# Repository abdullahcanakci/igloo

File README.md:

I have one of those led strips which controlled with a colorful remote and shows you the rainbow. I like them, setting the mood up so I can spend time on dark themed environments, or not having to get up after I'm done for the night and want some sleep.
But I think they lack some of those IOT and modern electronics magic we get used to. I only have cheap ones, not those philips hue or some other brand. 
The ones I have, has 20 preconfigured color and 4 different seizure inducing modes, can alter brightness. Everthing is fine and dandy. But if you want to have another color, too bad. Want to turn your home something other than a disco, no mode for that.

In my mind perfect control device should have:
1. Can alter colors without any limit.
2. Can alter modes without any limit.
3. Set auto on-off setting.
4. Can controlled from old school remotes.
5. Integration.

## 1 - Coloring

It just PWM how hard can it be. 

Right now I'm leaning into 3 color channels + 1 common channel. From my market search most of these strips are common VCC and RGB, there are some RGBW but not really widespread, at least in my country.

## 2 - Modes

The ones I have seen have

- Strobe
- Fade
- Ones above but with different colors.

I think these are not really nice modes, fade is somewhat bearable. Having ability to change fade colors, times and looping would be great, one can achieve so much with mere settings. 

## 3 - Auto

Automatic off would be nice set a timeout and let it fade out, or set a timer and wake up to fake sunset in the middle of winter.

## 4 - Remote

Although having a network connection is great we can't be certain a networked device would be avaible for, this reason there should be sane defaults, and ability to set any random IR remote as remote would be great. 

## 5 - Integration

I though about a bit about how can I implement multi device, controller etc in a system only composed of ESP12. It is not actually hard, but I didn't like the complexity of doing it all in C++, with some half-baked http library.

Thinking about Raspberry Pi Mini, an idea occurred, lets make a rPi a host, that applicable devices can connect, this way, I only need to create a web server to handle "User Interaction" on rPi, and it will pass down relevant data to controllers. This way I don't have to implement so much in ESP12's constraints. This has significant positives:

- Only need to create one web app to handle multi devices.
- Ease of adding and removing devices to system
  - Old way, I have to add a device to a network and set it up, and use it alone. This way, a newly added device can search the network for a compliant device and set up a connection and set the device up. After we can manage the controller device with the unified webapp.
- Ease of extensibility. 
  - Host system can be updated to handle more types of devices.
  - Host can be changed with a compliant system.
  - Host can implement third party home automation systems.
- Can update controller systems through air? Should be possible, have seen it, need to check how to implement it.

## Hardware

I have a look at some devices to use

- Raspberry Pi mini as host device. May create a hat for it to act as also, but not really sure about it.

- ESP12, is a good choice for sole pwm controlling job. It can do 200Hz refresh rate with 5ms downtime with software pwm. For hardware pwm, it has limited(2?) channels and not enough PWM counters to handle 3 different pwm channels.
- IRLML0030TRBF (TR Tape reel, BF ?), is a great little mosfet.
  - SOT23, so small
  - V_gth = 2.9V, which is great for most microcontrollers
  - Rds_on = 40mΩ @ 4.5V up to 4.2 amp continuos current. Which is plenty. Will mean ~50W @ 12V per channel. Prolly should limit it about 30W for 10 meter of 3W/m strip per channel.
  - PD of 0.65W @3.3V gate voltage 4 amp current, which will create a junction temperature of 65°C over ambient.
  - Not expensive @ 0.42$ per piece.
- Board will be 2 layers, preferably smaller than 40x60mm.

### Hardware Design

---

I have finally finished the hardware for led controller. It took some time, but I'm happy with the final product. While I was on the drawing board, I considered driving mosfets with pins from ESP12, which would work fine. But the specifications of the mosfet only provides values down to 4.5V which is 33mΩ. At 3.3V I was not in a safe spot to use the mosfet to it's limits. So I constructed a front end for every channel which consists of 1 PNP and 1 NPN transistor and few resistors. This enabled me to raise gate voltage of the mosfet to ~10.8V which Rds<sub>on</sub> = 22mΩ. Reduces resistance will achieve better thermals duty cycle is close to %100. Also by using transistors, mosfet gate charge time will be shorter which means mosfet will spend less time on the high resistance zones which also will help me to achieve better thermals. Cost for the extra transistors is negligible. They cost about 0.10$ to 0.15$ per 20 to 25 piece.

Final board size ended up at 50mm by 55mm which is great. While designing the board 40x60 was a bit optimistic but in the end it is only off by %15.

Power dissipation is fine at 10.8V gate voltage, 5.2A current. Resistive losses are @ 0.89W which will raise temperature to 90°C over ambient. Switching losses should be fine. By using transistors I reduced time to charge the gate capacitor. Also ESP12 will most likely run the PWM @ 1KHz which is pretty low, in this situation resistive losses will be the driving force. 

I used [this](https://www.electronicdesign.com/boards/calculate-dissipation-mosfets-high-power-supplies) website to help me with power dissipation.

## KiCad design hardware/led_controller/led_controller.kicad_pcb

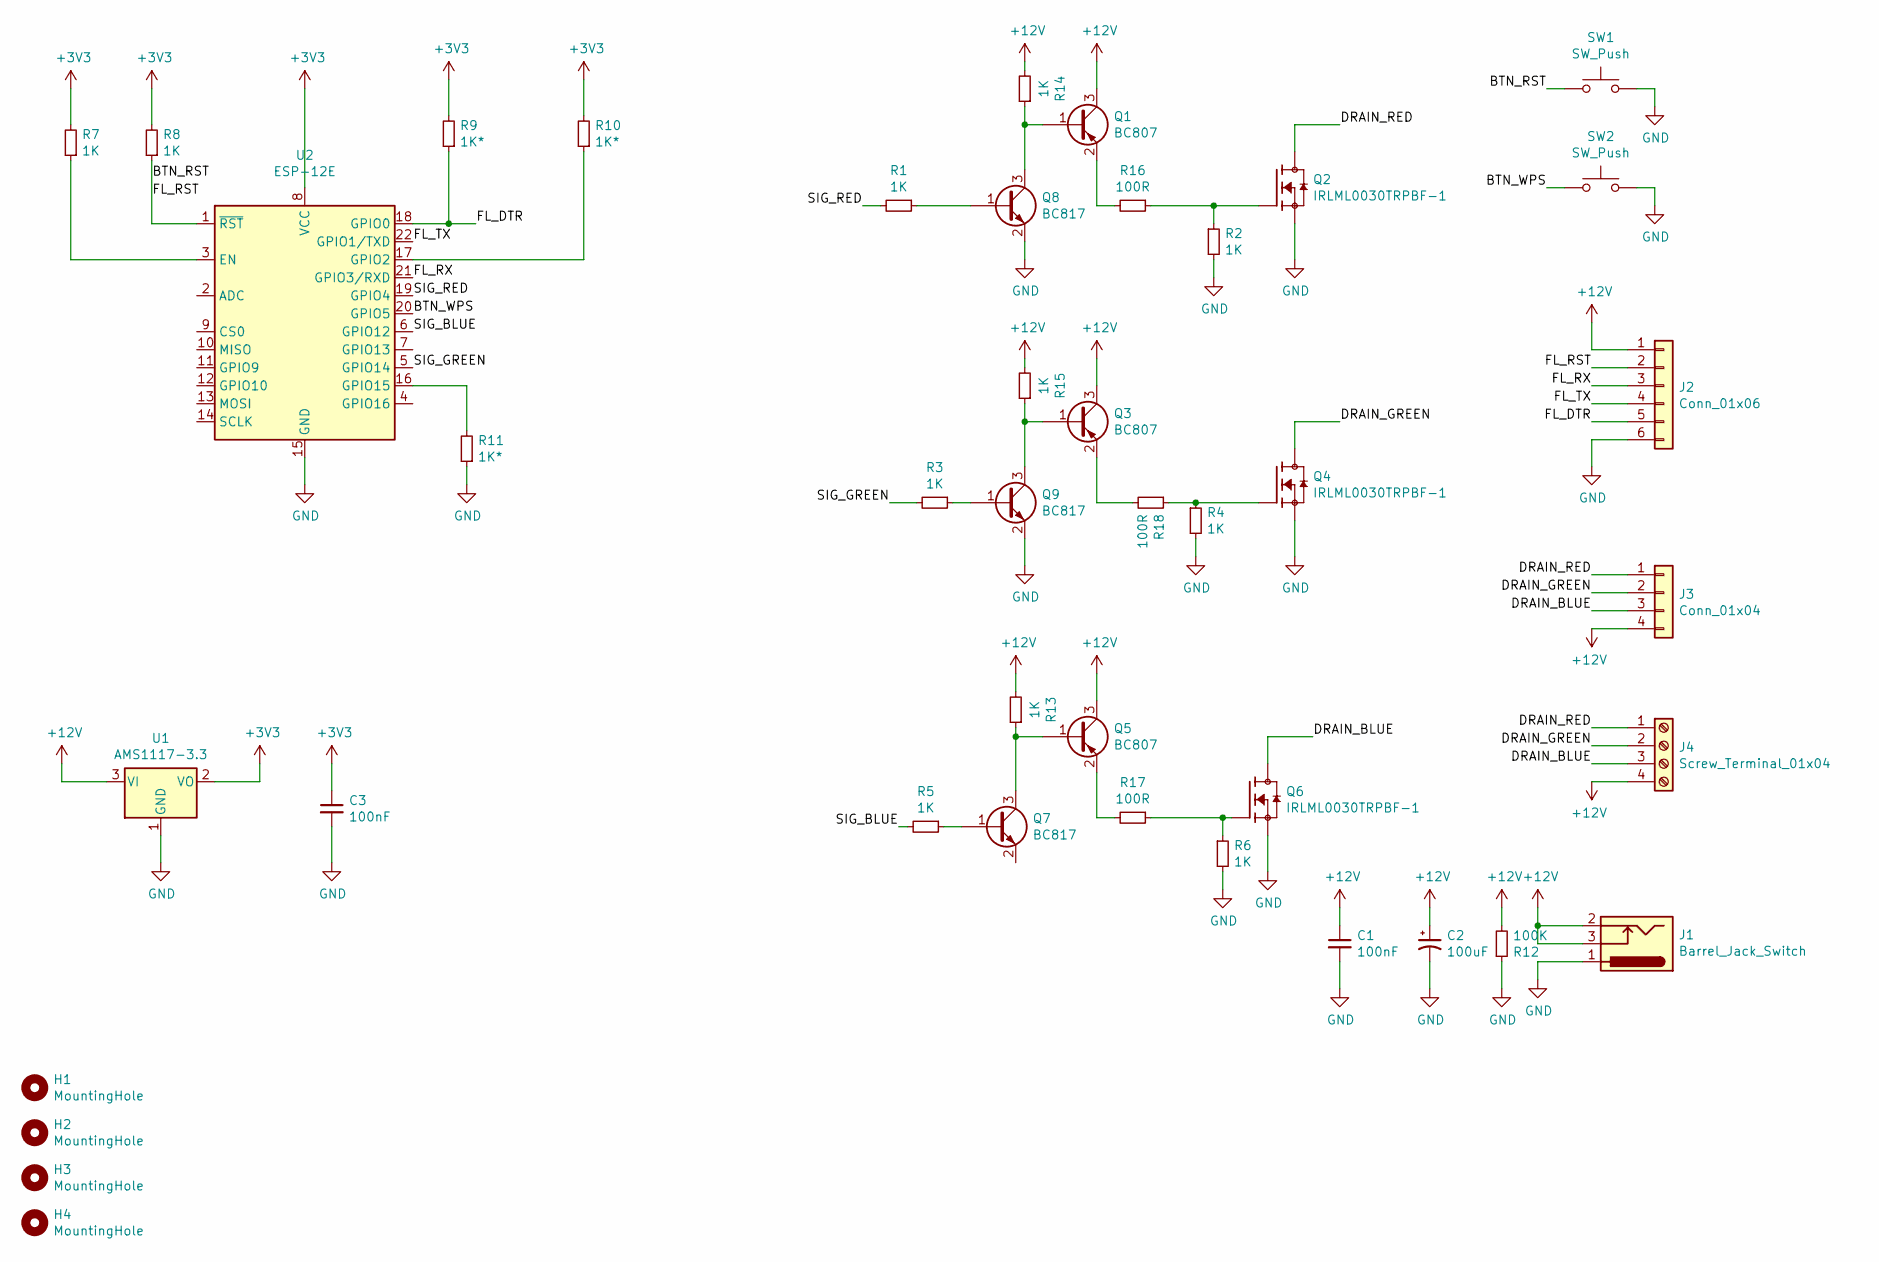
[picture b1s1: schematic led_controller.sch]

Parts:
C1, C3: 100nF; C_0805_2012Metric_Pad1.15x1.40mm_HandSolder
C2: 100uF; CP_Radial_D10.0mm_P2.50mm_P5.00mm
H1, H2, H3, H4: MountingHole; MountingHole_3.2mm_M3
J1: Barrel_Jack_Switch; BarrelJack_Horizontal
J2: Conn_01x06; PinHeader_1x06_P2.54mm_Vertical
J3: Conn_01x04; PinHeader_1x04_P2.54mm_Vertical
J4: Screw_Terminal_01x04; TerminalBlock_RND_205-00047_1x04_P5.00mm_Horizontal
Q1, Q3, Q5: BC807; SOT-23
Q2, Q4, Q6: IRLML0030TRPBF-1; SOT95P237X112-3N
Q7, Q8, Q9: BC817; SOT-23
R1, R2, R3, R4, R5, R6, R7, R8, R13, R14, R15: 1K; R_0805_2012Metric_Pad1.15x1.40mm_HandSolder
R9, R10, R11: 1K*; R_0805_2012Metric_Pad1.15x1.40mm_HandSolder
R12: 100K; R_0805_2012Metric_Pad1.15x1.40mm_HandSolder
R16, R17, R18: 100R; R_0805_2012Metric_Pad1.15x1.40mm_HandSolder
SW1, SW2: SW_Push; SW_Push_1P1T_NO_6x6mm_H9.5mm
U1: AMS1117-3.3; SOT-223-3_TabPin2
U2: ESP-12E

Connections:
+3V3: C3.1, R7.2, R8.2, R9.2, R10.2, U1.2 (VO), U2.8 (VCC)
+12V: C1.1, C2.1, J1.2, J1.3, J2.1, J3.4, J4.4, Q1.3 (C), Q3.3 (C), Q5.3 (C), R12.2, R13.2, R14.2, R15.2, U1.3 (VI)
/BTN_RST: J2.2, R8.1, SW1.1, U2.1 (~RST)
/BTN_WPS: SW2.1, U2.20 (GPIO5)
/DRAIN_BLUE: J3.3, J4.3, Q6.3 (D)
/DRAIN_GREEN: J3.2, J4.2, Q4.3 (D)
/DRAIN_RED: J3.1, J4.1, Q2.3 (D)
/FL_DTR: J2.5, R9.1, U2.18 (GPIO0)
/FL_RX: J2.3, U2.21 (GPIO3/RXD)
/FL_TX: J2.4, U2.22 (GPIO1/TXD)
/SIG_BLUE: R5.2, U2.6 (GPIO12)
/SIG_GREEN: R3.2, U2.5 (GPIO14)
/SIG_RED: R1.2, U2.19 (GPIO4)
GND: C1.2, C2.2, C3.2, J1.1, J2.6, Q2.2 (S), Q4.2 (S), Q6.2 (S), Q8.2 (E), Q9.2 (E), R2.2, R4.2, R6.2, R11.1, R12.1, SW1.2, SW2.2, U1.1 (GND), U2.15 (GND)
unnamed: Q1.1 (B), Q8.3 (C), R14.1
unnamed: Q1.2 (E), R16.2
unnamed: Q2.1 (G), R2.1, R16.1
unnamed: Q3.1 (B), Q9.3 (C), R15.1
unnamed: Q3.2 (E), R18.2
unnamed: Q4.1 (G), R4.1, R18.1
unnamed: Q5.1 (B), Q7.3 (C), R13.1
unnamed: Q5.2 (E), R17.2
unnamed: Q6.1 (G), R6.1, R17.1
unnamed: Q7.1 (B), R5.1
unnamed: Q8.1 (B), R1.1
unnamed: Q9.1 (B), R3.1
unnamed: R7.1, U2.3 (EN)
unnamed: R10.1, U2.17 (GPIO2)
unnamed: R11.2, U2.16 (GPIO15)

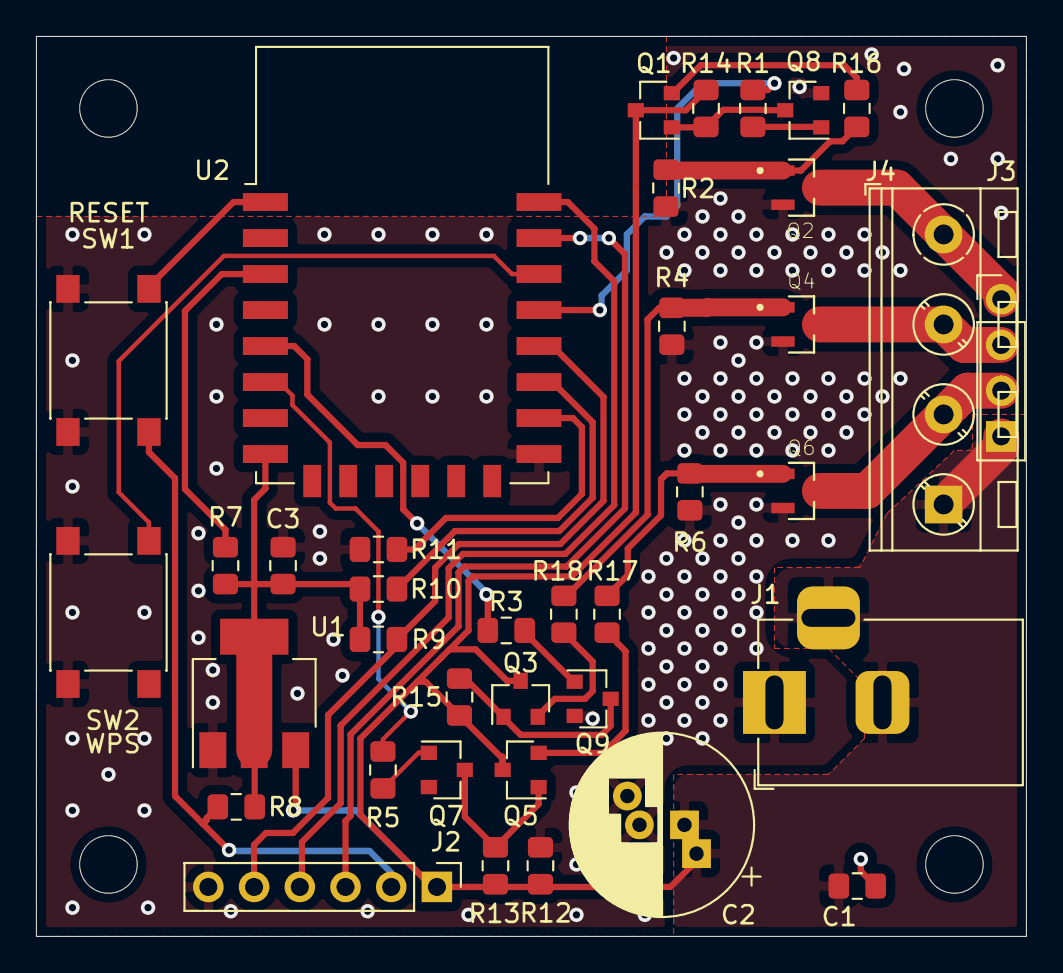
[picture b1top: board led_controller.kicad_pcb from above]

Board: 2 copper layers, 55.0 x 50.0 mm, 42 parts (0 on the bottom side), 29 nets.

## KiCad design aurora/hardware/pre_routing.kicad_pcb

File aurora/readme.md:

# Preface

I have one of those led strips with a colorful remote to control it. Most people have them, they are cheap, they are easy to install and most important of all abundant.

If I have to find a problem with them, it would be their horrendous controls. They have all the colors needed for full spectrum color creation, but their control circuitry only allows about 20 colors and 10 brightness settings.

I would like to have a controller with precise color control,  multiple modes to use and somewhat smart so it can act on predefined triggers.

Aim of the Aurora project is to create a led strip controller.

[Workspace Set-up](workspace.md)

## Requirements

1. High color range.
2. Multiple modes to use.
3. Actions by predefined triggers.
4. Integrated or solo use.
5. Preferably remote controlled.

### Led Control

Most of the generic led strips I have found contains RGB sink channels and 1 common VCC one. These are generally powered by 12V dedicated power supplies. There are some 4 color strips which includes white but they are not really common.

Each color channel will be controlled by a dedicated mosfet circuitry. These circuits will be driven by a micro controller in PWM achieve fine grained control.

#### Brightness

Controlling brightness of a led emitting diode is hard. On a led display a backlight is used to illuminate the colored substrate. If you want to control it's brightness you reduce the duty cycle of backlight to achieve different brightness levels. In light emitting diodes each color led is producing it's own light and reducing brightness by clamping duty cycle of  said led will create different color ranges on different brightness levels which can be observed on devices using OLED technology.

There are 2 different ways to tackle this problem. Making the brightness a logarithmic curve, so color range loss will be less visible is easier one but also the problem will still persist. Other one is, defining 3 color channels as 1 channel and controlling the duty cycle of this main channel. In the end we will achieve better color accuracy.

#### Coloring

Creating a color mix of 3 different light sources is easy with controlling duty cycle of each color channel.

### Modes

Lightning modes available on a commercial device at best is lacking. Strobe, fade, flash and few more. They are all uncomfortable. I don't really know if a good mode can be found to implement.

#### Fade

After the user changed the color, displayed color will be fade to the new color.

### Trigger

Led drivers are dumb as in they do not have a memory to act on and can not act upon triggers from outside. 

Outside trigger can be a set time where the device turns on. A loop it can run through or something that does not come as easily.

### Remote 

Although having a network connection is great we can't be certain a networking device will be available, this reason if we can integrate IR receiver so it can controllable by remotes would be good.

I have checked [Arduino-IRremote](https://github.com/z3t0/Arduino-IRremote) library to understand how they handle IR signal receiving and conversion. It uses an interrupt with 50 nanosecond interval. I don't think I can afford that with RTOS, network and led switching. I will check if it can be done but it does not looks promising.

### Integration

I am designing this device to be used within a larger ecosystem. 

To use within the ecosystem, a host device must be available on the network to connect.

## Hardware

- ESP12 is a micro controller with network integration and high storage space. 
- IRLML0030
  - SOT23 - so small
  - Rds<sub>on_normalized</sub> = 33mΩ at 10.8V gate voltage with 5 Amp current
  - 0.8W power dissipation @ 5Amp current
  - 0.42$ per piece
- BC807 - BC817, as mosfet driver circuit.
  - Widely available
  - 0.10$ per 20/25 piece
- 6mm tactile buttons for interaction
- 100-470 uF elec cap
- DC jack for power input

- Terminal strip or pin headers for led strip connections.
- required surface mount capacitors and resistor.

PCB with 2 layers preferably smaller than 50x60mm. Square?

# Application

Before any software development I would like to design the device schematic to be finished. Reason is I would like to test every step of software as I developed.

## Hardware Design

1. Power and led connections should be on the same side.
2. Buttons should be on the opposite side of the power connection.
3. Preferably screw points around connection points.
4. Programming connection.
5. Large ground areas around mosfets.

Driving mosfets with micro controller pins are not a wise move. With high current and slow gate charge times, switching losses would be high. If I use 3 transistors per channel I can drive mosfets with high current at 10.8V.

Power dissipation is fine at 10.8V gate voltage, 5.2A current. Resistive losses are @ 0.89W which will raise temperature to 90°C over ambient. Switching losses should be fine. By using transistors I reduced time to charge the gate capacitor. Also ESP12 will most likely run the PWM @ 200Hz which is pretty low, in this situation resistive losses will be the driving force. 

I used [this](https://www.electronicdesign.com/boards/calculate-dissipation-mosfets-high-power-supplies) website to help me with power dissipation.

# Software Requirements

2 operation modes. Slave mode and solo mode. 

Selection will be done with the FUNC button on the device. If the button is depressed on the boot sequence it will enter the solo mode, if not slave mode will initiate.

After the device boot FUNC button will have 2 different roles. Short press will toggle the light status. Holding the button will activate network settings. In network mode holding the button will start the WPS process, short pressing it will start a network interface to connect with another device to set it up. In this state the user can define network properties, and device settings. Next boot will use updated settings

Slave mode will be used with host device and only will be controlled through unified interface of host device. Aurora won't connect to the internet in this mode, will pull time information from host device.

Solo mode will need a driver application or mqqt server to handle it.

Requirements:

1. Boot sequence state machine.
2. Time based interrupts.
3. Led control routine.
4. Led control interface.
5. Led control web interface.
6. Solo mode web user interface
7. Slave mode interface

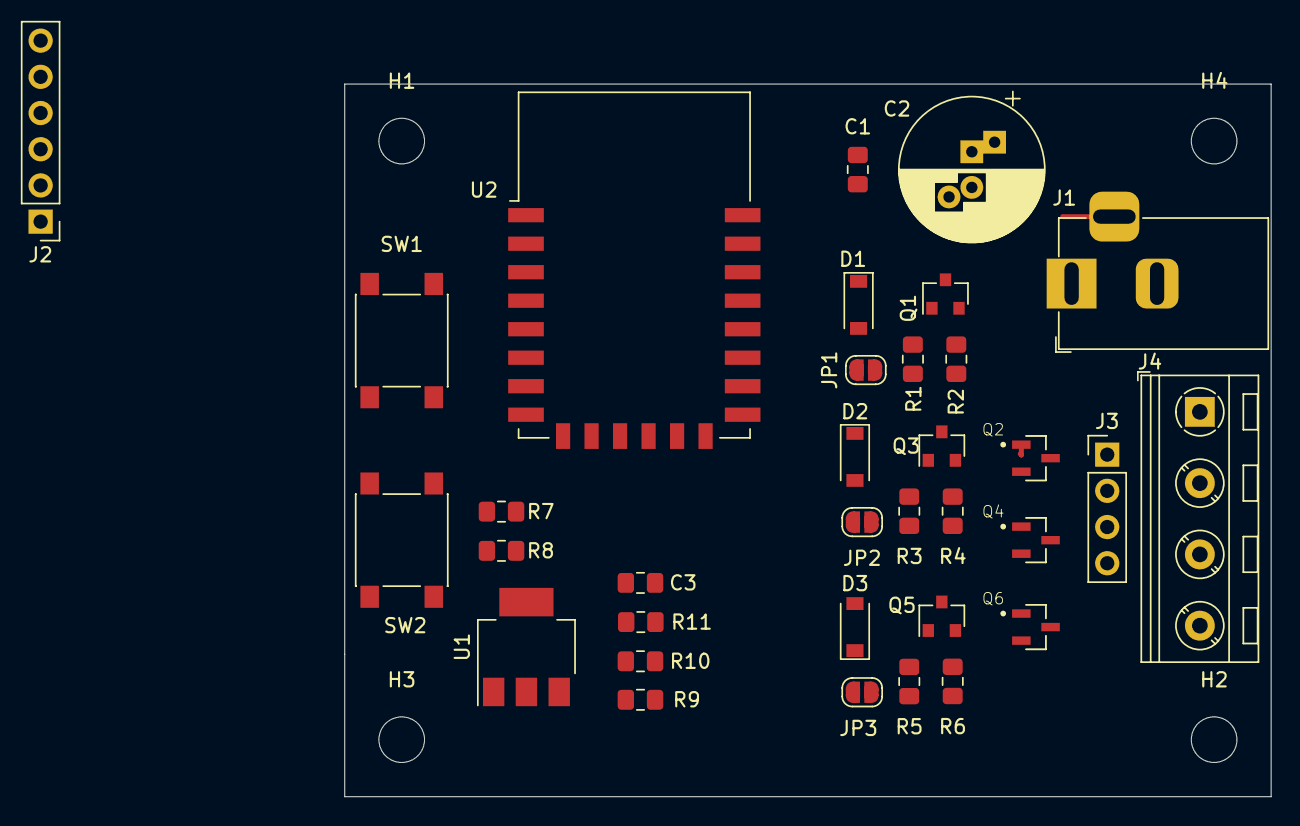
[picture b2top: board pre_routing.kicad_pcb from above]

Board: 2 copper layers, 65.0 x 50.0 mm, 38 parts (0 on the bottom side), 23 nets.

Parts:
C1, C3: 100nF; C_0805_2012Metric_Pad1.15x1.40mm_HandSolder
C2: 100uF; CP_Radial_D10.0mm_P2.50mm_P5.00mm
D1, D2, D3: 1N4148W; D_SOD-123
H1, H2, H3, H4: MountingHole; MountingHole_3.2mm_M3
J1: Barrel_Jack_Switch; BarrelJack_Horizontal
J2: Conn_01x06; PinHeader_1x06_P2.54mm_Vertical
J3: Conn_01x04; PinHeader_1x04_P2.54mm_Vertical
J4: Screw_Terminal_01x04; TerminalBlock_RND_205-00047_1x04_P5.00mm_Horizontal
JP1: Red; SolderJumper-2_P1.3mm_Open_RoundedPad1.0x1.5mm
JP2: Green; SolderJumper-2_P1.3mm_Open_RoundedPad1.0x1.5mm
JP3: Blue; SolderJumper-2_P1.3mm_Open_RoundedPad1.0x1.5mm
Q1, Q3, Q5: BC807; SOT-23
Q2, Q4, Q6: IRLML0030TRPBF-1; SOT95P237X112-3N
R1, R3, R5, R7, R8: 1K; R_0805_2012Metric_Pad1.15x1.40mm_HandSolder
R2, R4, R6: 100R; R_0805_2012Metric_Pad1.15x1.40mm_HandSolder
R9, R10, R11: 1K*; R_0805_2012Metric_Pad1.15x1.40mm_HandSolder
SW1, SW2: SW_Push; SW_Push_1P1T_NO_6x6mm_H9.5mm
U1: AMS1117-3.3; SOT-223-3_TabPin2
U2: ESP-12E

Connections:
+3V3: C3.1, R7.2, R8.2, R9.2, R10.2, U1.2, U2.8
+12V: C1.1, C2.1, J1.2, J1.3, J2.1, J3.1, J4.1, Q1.3, Q3.3, Q5.3, U1.3
/BTN_WPS: SW2.1, U2.20
/DRAIN_BLUE: J3.4, J4.4, Q6.3
/DRAIN_GREEN: J3.3, J4.3, Q4.3
/DRAIN_RED: J3.2, J4.2, Q2.3
/FL_DTR: J2.5, R9.1, U2.18
/FL_RX: J2.3, U2.21
/FL_TX: J2.4, U2.22
/SIG_BLUE: JP3.1, R5.2
/SIG_GREEN: JP2.1, R3.2
/SIG_RED: JP1.1, R1.2
GND: C1.2, C2.2, C3.2, J1.1, J2.6, Q2.2, Q4.2, Q6.2, R2.2, R4.2, R6.2, R11.1, SW1.2, SW2.2, U1.1, U2.15
unnamed: D1.1, Q1.1, R1.1
unnamed: D1.2, JP1.2, Q1.2, Q2.1, R2.1
unnamed: D2.1, Q3.1, R3.1
unnamed: D2.2, JP2.2, Q3.2, Q4.1, R4.1
unnamed: D3.1, Q5.1, R5.1
unnamed: D3.2, JP3.2, Q5.2, Q6.1, R6.1
unnamed: R7.1, U2.3
unnamed: R8.1, U2.1
unnamed: R10.1, U2.17
unnamed: R11.2, U2.16

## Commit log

2019-10-19 updated readme, created kicad project
2019-11-19 Updated readme \n\n Raspberry pi usage
2019-12-07 hardware init
2019-12-07 createad schematic and routed the pcb
2019-12-07 Removed bakers clamps. reduced board size to 55x50 mm
2019-12-08 finished board design
2019-12-09 Modified connectors and silkscreens. Added a diode to keep capacitor from charging during flashing. Added a second layer to mosfet connector traces and stiched them to help power dissipation.
2019-12-13 Reorganized project files. Divide up readme file
2019-12-20 added software requirements for Aurora
2019-12-21 Added workspace setup
2019-12-21 fix a path error
2019-12-21 Create LICENSE
2019-12-22 Added proto firmware for the device. Implemented a cyclic buffer for future use.
2019-12-22 Basic button debouncing and pin interrupts
2019-12-23 Button debouncing click+hold implemented. System timer added.
2019-12-24 updated workspace document
2019-12-24 basic wps implementation
2019-12-24 Added WIFI and WPS integration
2019-12-24 Readme updates
